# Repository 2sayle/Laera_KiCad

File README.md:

# Laera Project : KiCad Design
Laera is tiny air quality monitoring dongle using LoRa

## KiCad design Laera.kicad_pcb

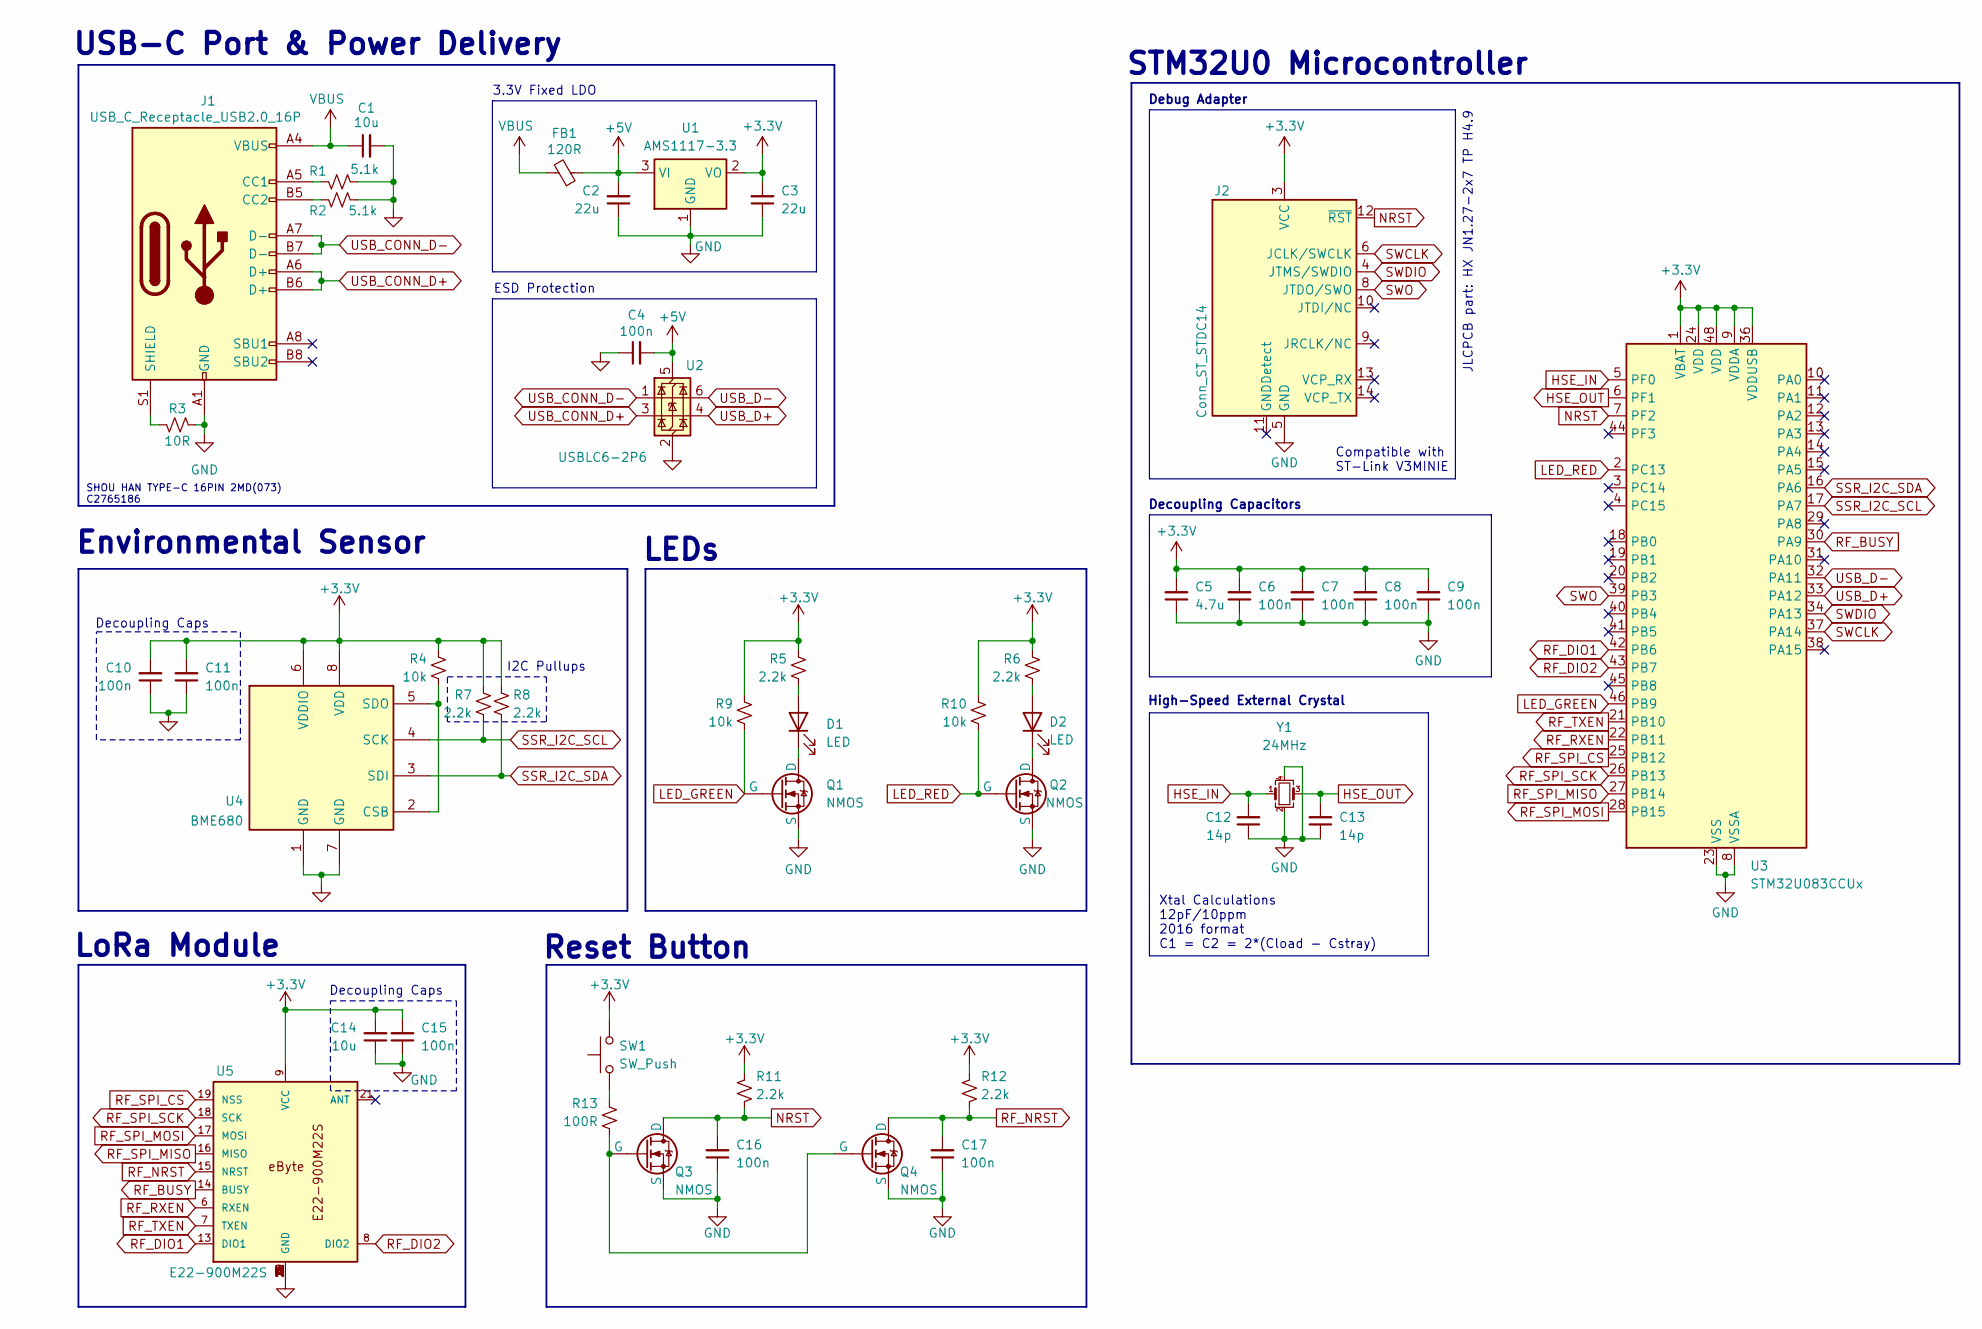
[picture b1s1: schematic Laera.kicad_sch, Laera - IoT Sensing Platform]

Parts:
C1, C14: 10u; C_0603_1608Metric
C2, C3: 22u; C_0603_1608Metric
C4, C6, C7, C8, C9, C10, C11, C15, C16, C17: 100n; C_0603_1608Metric
C5: 4.7u; C_0603_1608Metric
C12, C13: 14p; C_0603_1608Metric
D1, D2: LED; LED_0603_1608Metric
FB1: 120R; L_0603_1608Metric
J1: USB_C_Receptacle_USB2.0_16P; CONN16_C16PIN_SHN
J2: Conn_ST_STDC14; J_Wurth_WR-BHD_62701420621
Q1, Q2, Q3, Q4: NMOS; SOT-23
R1, R2: 5.1k; R_0603_1608Metric
R3: 10R; R_0603_1608Metric
R4, R9, R10: 10k; R_0603_1608Metric
R5, R6, R7, R8, R11, R12: 2.2k; R_0603_1608Metric
R13: 100R; R_0603_1608Metric
SW1: SW_Push; SW_Push_1P1T_NO_CK_KMR2
U1: AMS1117-3.3; SOT-223-3_TabPin2
U2: USBLC6-2P6; SOT-666
U3: STM32U083CCUx; QFN-48-1EP_7x7mm_P0.5mm_EP5.6x5.6mm
U4: BME680; Bosch_LGA-8_3x3mm_P0.8mm_ClockwisePinNumbering
U5: E22-900M22S
Y1: 24MHz; Crystal_SMD_2016-4Pin_2.0x1.6mm

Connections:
+3.3V: C3.2, C5.2, C6.2, C7.2, C8.2, C9.2, C10.2, C11.2, C14.2, C15.2, J2.3 (VCC), R4.2, R5.2, R6.2, R7.2, R8.1, R9.2, R10.2, R11.2, R12.2, SW1.2, U1.2 (VO), U3.1 (VBAT), U3.9 (VDDA), U3.24 (VDD), U3.36 (VDDUSB), U3.48 (VDD), U4.6 (VDDIO), U4.8 (VDD), U5.9 (VCC)
+5V: C2.2, C4.2, FB1.1, U1.3 (VI), U2.5 (VBUS)
GND: C1.2, C2.1, C3.1, C4.1, C5.1, C6.1, C7.1, C8.1, C9.1, C10.1, C11.1, C12.1, C13.1, C14.1, C15.1, C16.1, C17.1, J1.A1 (GND), J1.A12 (GND), J1.B1 (GND), J1.B12 (GND), J2.5 (GND), J2.7 (GND), Q1.3 (S), Q2.3 (S), Q3.3 (S), Q4.3 (S), R1.1, R2.1, R3.1, U1.1 (GND), U2.2 (GND), U3.8 (VSSA), U3.23 (VSS), U3.35 (VSS), U3.47 (VSS), U3.49 (VSS), U4.1 (GND), U4.7 (GND), U5.1 (GND), U5.2 (GND), U5.3 (GND), U5.4 (GND), U5.5 (GND), U5.10 (GND), U5.11 (GND), U5.12 (GND), U5.20 (GND), U5.22 (GND), Y1.2, Y1.4
HSE_IN: C12.2, U3.5 (PF0), Y1.1
HSE_OUT: C13.2, U3.6 (PF1), Y1.3
LED_GREEN: Q1.2 (G), R9.1, U3.46 (PB9)
LED_RED: Q2.2 (G), R10.1, U3.2 (PC13)
NRST: C16.2, J2.12 (~RST), Q3.1 (D), R11.1, U3.7 (PF2)
unnamed: D1.2 (A), R5.1
unnamed: D1.1 (K), Q1.1 (D)
unnamed: D2.2 (A), R6.1
unnamed: D2.1 (K), Q2.1 (D)
unnamed: J1.A5 (CC1), R1.2
unnamed: J1.B5 (CC2), R2.2
unnamed: J1.S1 (SHIELD), R3.2
unnamed: Q3.2 (G), Q4.2 (G), R13.1
unnamed: R13.2, SW1.1
unnamed: R4.1, U4.2 (CSB), U4.5 (SDO)
RF_BUSY: U3.30 (PA9), U5.14 (BUSY)
RF_DIO1: U3.42 (PB6), U5.13 (DIO1)
RF_DIO2: U3.43 (PB7), U5.8 (DIO2)
RF_NRST: C17.2, Q4.1 (D), R12.1, U5.15 (NRST)
RF_RXEN: U3.22 (PB11), U5.6 (RXEN)
RF_SPI_CS: U3.25 (PB12), U5.19 (NSS)
RF_SPI_MISO: U3.27 (PB14), U5.16 (MISO)
RF_SPI_MOSI: U3.28 (PB15), U5.17 (MOSI)
RF_SPI_SCK: U3.26 (PB13), U5.18 (SCK)
RF_TXEN: U3.21 (PB10), U5.7 (TXEN)
SSR_I2C_SCL: R7.1, U3.17 (PA7), U4.4 (SCK)
SSR_I2C_SDA: R8.2, U3.16 (PA6), U4.3 (SDI)
SWCLK: J2.6 (JCLK/SWCLK), U3.37 (PA14)
SWDIO: J2.4 (JTMS/SWDIO), U3.34 (PA13)
SWO: J2.8 (JTDO/SWO), U3.39 (PB3)
USB_CONN_D+: J1.A6 (D+), J1.B6 (D+), U2.3 (I/O2)
USB_CONN_D-: J1.A7 (D-), J1.B7 (D-), U2.1 (I/O1)
USB_D+: U2.4 (I/O2), U3.33 (PA12)
USB_D-: U2.6 (I/O1), U3.32 (PA11)
VBUS: C1.1, FB1.2, J1.A4 (VBUS), J1.A9 (VBUS), J1.B4 (VBUS), J1.B9 (VBUS)

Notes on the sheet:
Reset Button
STM32U0 Microcontroller
LoRa Module
Debug Adapter
Xtal Calculations 12pF/10ppm 2016 format C1 = C2 = 2*(Cload - Cstray)
Environmental Sensor
Decoupling Capacitors
Decoupling Caps
ESD Protection
JLCPCB part: HX JN1.27-2x7 TP H4.9
High-Speed External Crystal
Compatible with ST-Link V3MINIE
LEDs
USB-C Port & Power Delivery
SHOU HAN TYPE-C 16PIN 2MD(073) C2765186
I2C Pullups
3.3V Fixed LDO

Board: 4 copper layers, 46 parts (0 on the bottom side), 38 nets, no tracks yet.

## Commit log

2025-07-07 Added: First files and gitignore
2025-07-08 Finished ERC + Started Layout

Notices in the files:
Laera.kicad_sch:
All rights reserved.
